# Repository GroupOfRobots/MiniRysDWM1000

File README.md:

# RobotLocalization
DWM1000-based localization module repo.

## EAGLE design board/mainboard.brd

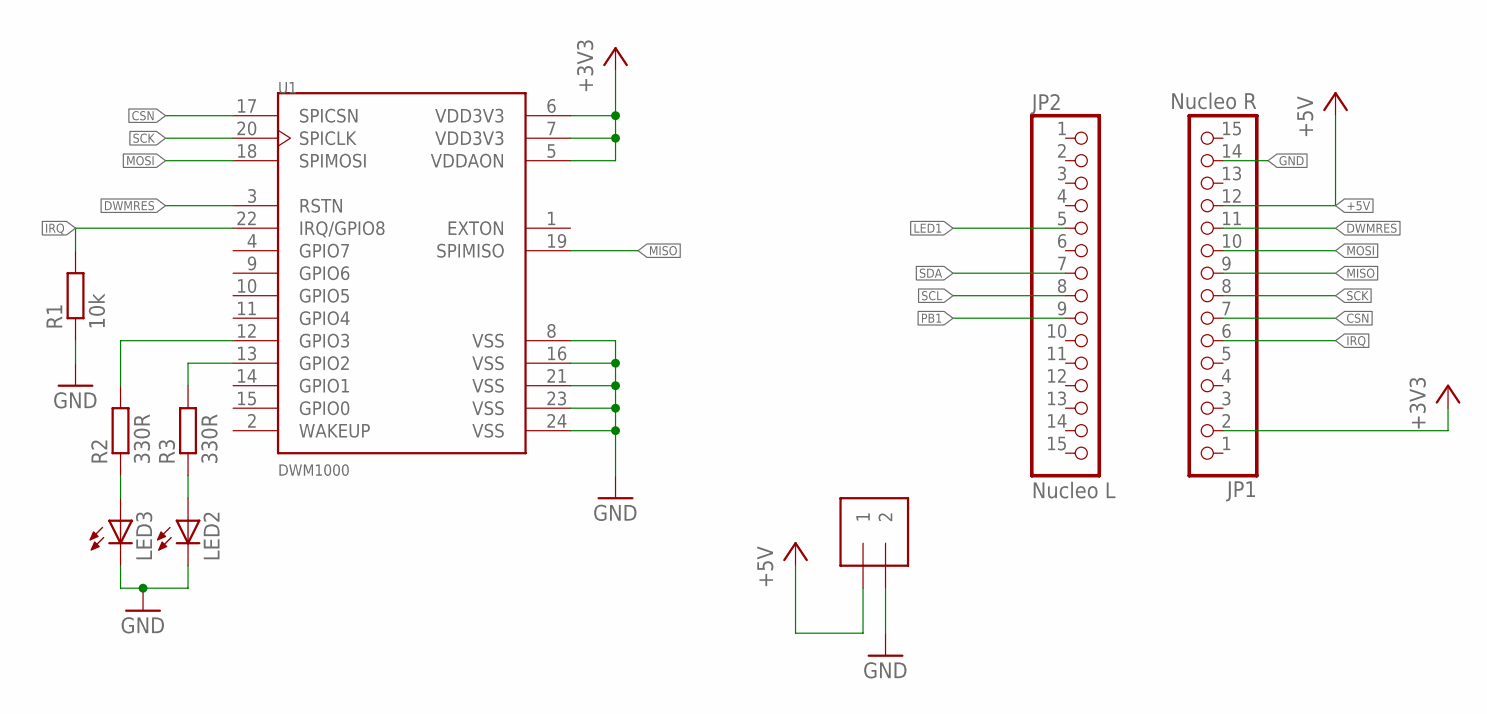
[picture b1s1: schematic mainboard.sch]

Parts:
J1: 1X2-3.5MM
JP1: Nucleo R; 1X15
JP2: Nucleo L; 1X15
LED2, LED3: LEDSML0603; SML0603
R1: 10k; R0603
R2, R3: 330R; R0603
U1: DWM1000; XCVR_DWM1000

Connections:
+3V3: JP1.2, U1.5 (VDDAON), U1.6 (VDD3V3), U1.7 (VDD3V3)
+5V: J1.1, JP1.12
CSN: JP1.7, U1.17 (SPICSN)
DWMRES: JP1.11, U1.3 (RSTN)
GND: J1.2, JP1.14, LED2.C, LED3.C, R1.1, U1.8 (VSS), U1.16 (VSS), U1.21 (VSS), U1.23 (VSS), U1.24 (VSS)
IRQ: JP1.6, R1.2, U1.22 (IRQ/GPIO8)
LED1: JP2.5
MISO: JP1.9, U1.19 (SPIMISO)
MOSI: JP1.10, U1.18 (SPIMOSI)
unnamed: R3.2, U1.13 (GPIO2)
unnamed: R2.2, U1.12 (GPIO3)
unnamed: LED2.A, R3.1
unnamed: LED3.A, R2.1
PB1: JP2.9
SCK: JP1.8, U1.20 (SPICLK)
SCL: JP2.8
SDA: JP2.7

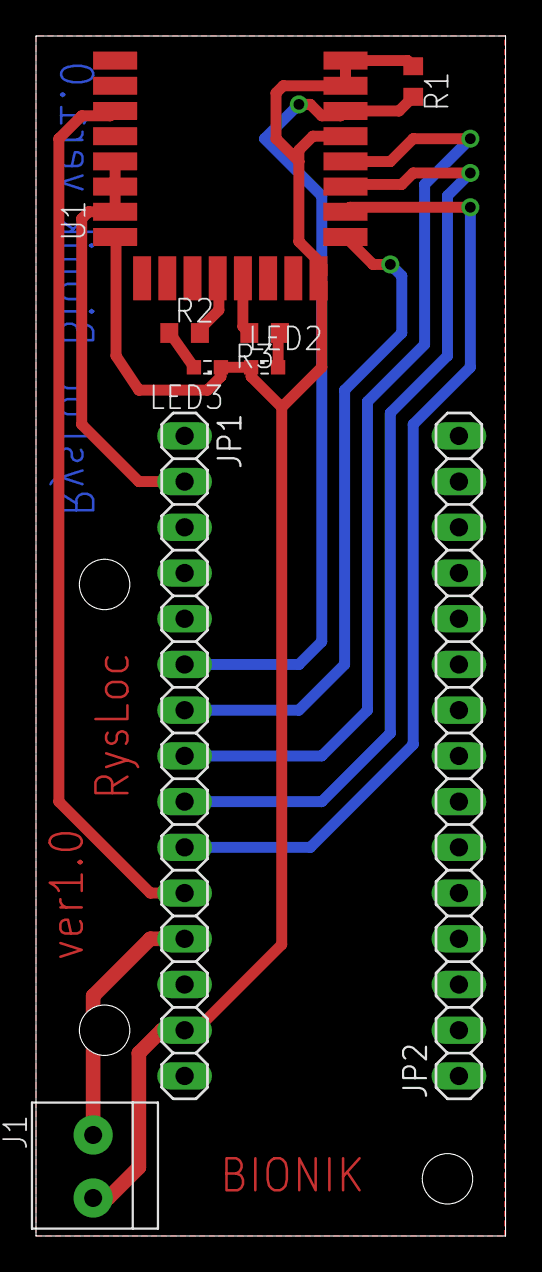
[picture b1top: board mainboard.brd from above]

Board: 2 copper layers, 26.1 x 66.7 mm, 9 parts (0 on the bottom side), 13 nets.

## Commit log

2017-01-25 add power switch and conn
2017-01-25 check dwm connections
2017-01-26 ready to gerber
2017-03-29 powerplug and mountings
2017-03-31 drill
2017-04-30 stat
2017-05-06 wysłane
2017-05-15 poprawione gerbery
